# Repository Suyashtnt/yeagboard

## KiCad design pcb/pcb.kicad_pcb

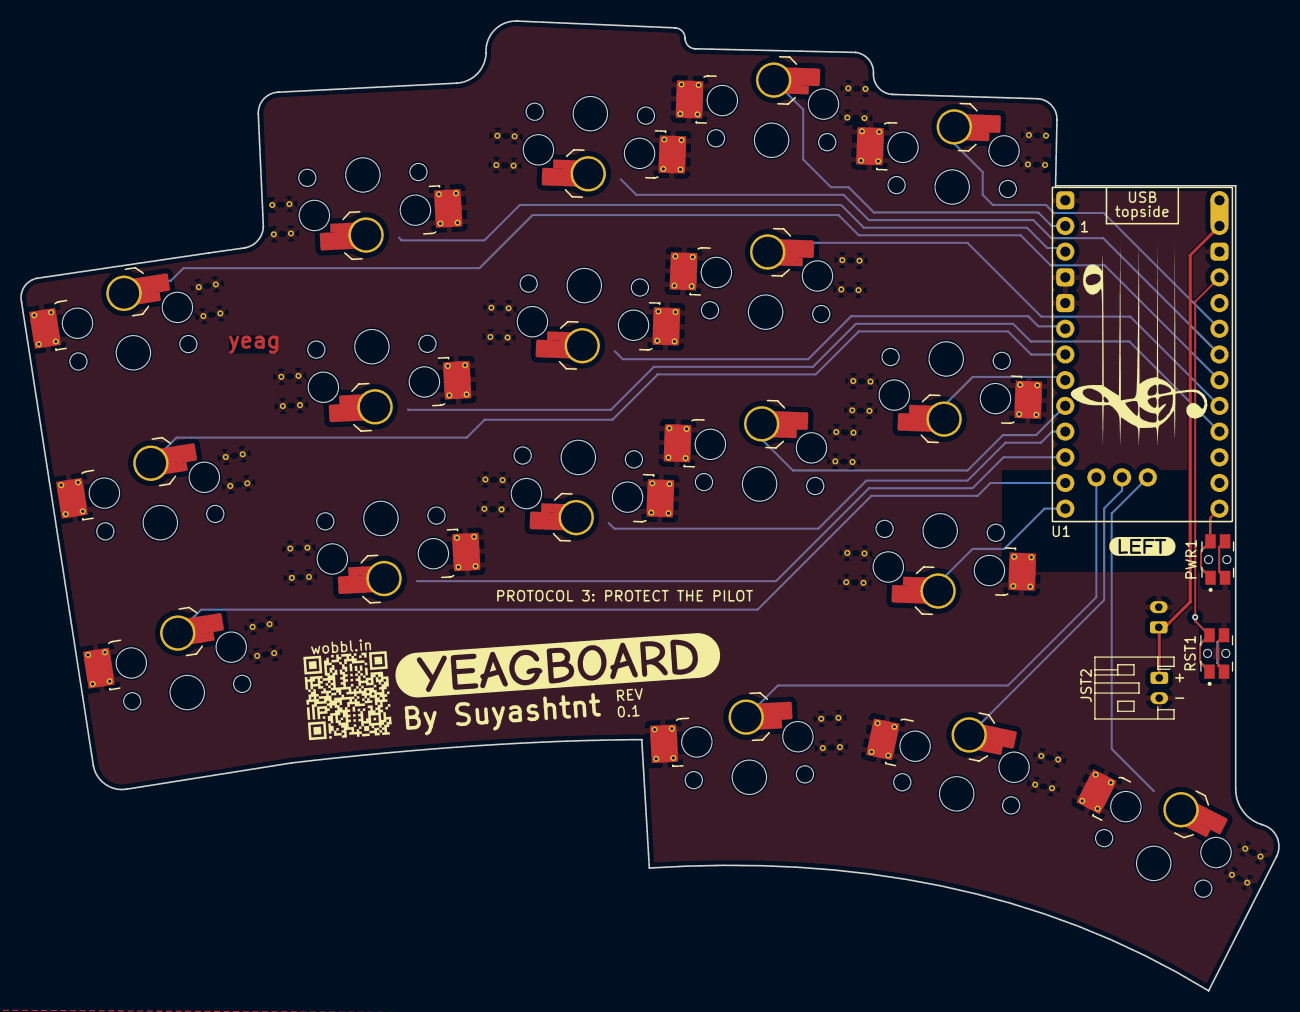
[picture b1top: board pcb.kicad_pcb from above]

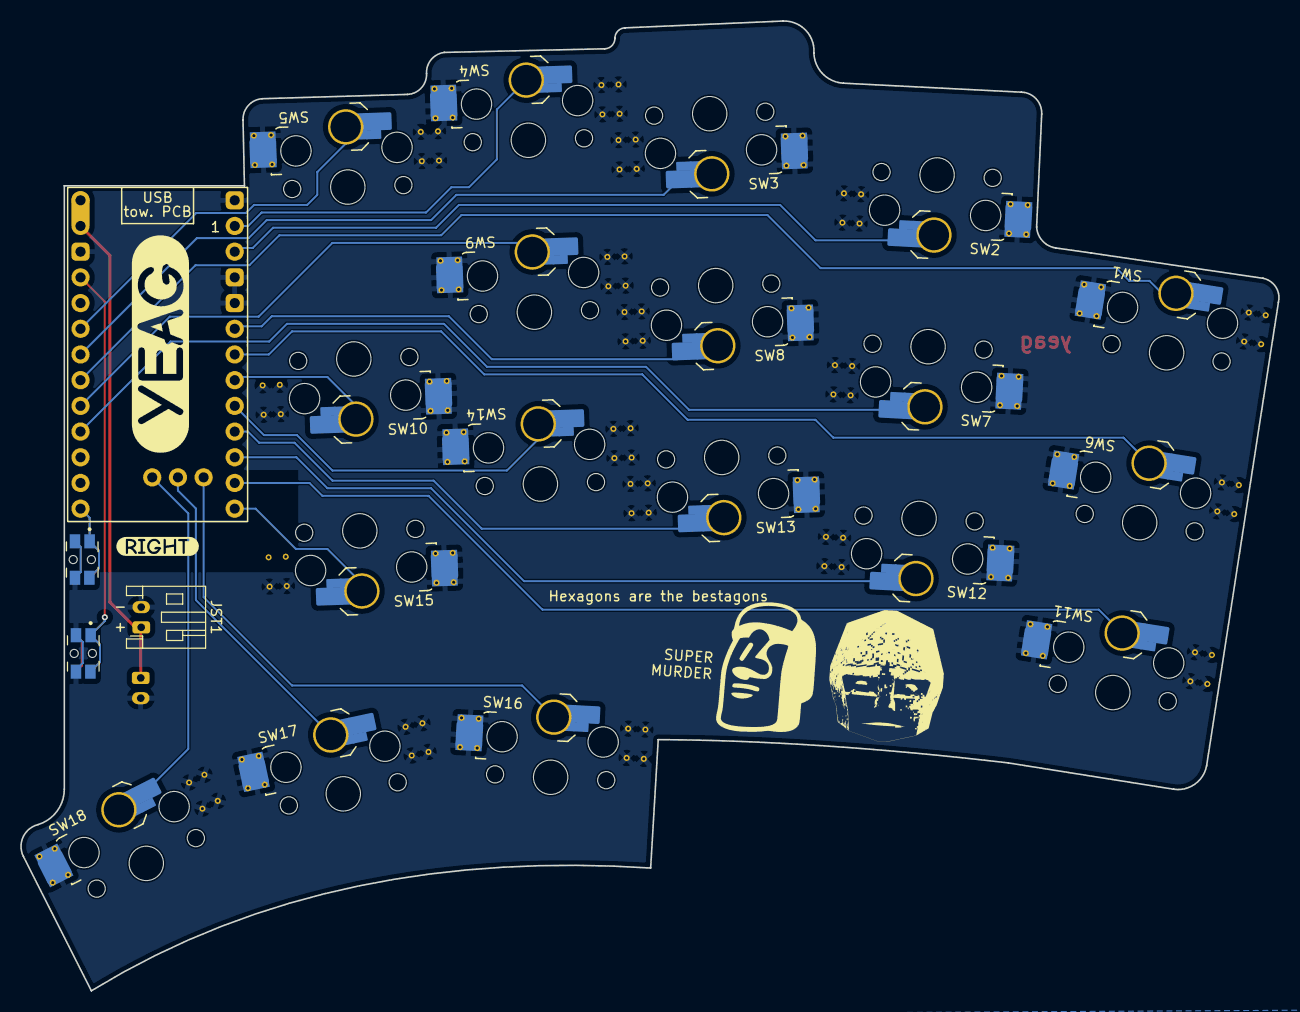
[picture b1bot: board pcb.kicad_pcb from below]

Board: 2 copper layers, 124.3 x 95.9 mm, 28 parts (21 on the bottom side), 22 nets.

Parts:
JST1, JST2: Conn_01x02; JST_PH_S2B-PH-K_1x02_P2.00mm_Horizontal
PWR1: EVQ-P7C01P; EVQ-P7C-Reversible
QR*****: WobblQR
RST1: EVQ-P7C01P; EVQ-P7C-Reversible
SW1, SW2, SW3, SW4, SW5, SW6, SW7, SW8, SW9, SW10, SW11, SW12, SW13, SW14, SW15, SW16, SW17, SW18: SW_Push; Choc-V1-HS-Reversible
U1: SuperMini nRF52840; SuperMini_nRF52840_AH_Reversible
kibuzzard-671E83A0: G***; kibuzzard-671E83A0
kibuzzard-671E83AE: G***; kibuzzard-671E83AE
kibuzzard-671E828F: G***; kibuzzard-671E828F
kibuzzard-671E8171: G***; kibuzzard-671E8171

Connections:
+BATT: JST1.1, JST2.1, U1.13 (BAT+), U1.29 (BAT+)
GND: JST1.2, JST2.2, PWR1.2, RST1.2, SW1.2, SW2.2, SW3.2, SW4.2, SW5.2, SW6.2, SW7.2, SW8.2, SW9.2, SW10.2, SW11.2, SW12.2, SW13.2, SW14.2, SW15.2, SW16.2, SW17.2, SW18.2, U1.3 (GND), U1.4 (GND), U1.14 (GND), U1.28 (GND)
PWR-BTN: PWR1.1, U1.24 (P0.09-LF)
RST: RST1.1, U1.15 (RST)
Switch1: SW1.1, U1.19 (P0.02-LF)
Switch2: SW2.1, U1.2 (P0.08)
Switch3: SW3.1, U1.18 (P0.29-LF)
Switch4: SW4.1, U1.1 (P0.06)
Switch5: SW5.1, U1.17 (P0.31-LF)
Switch6: SW6.1, U1.6 (P0.20)
Switch7: SW7.1, U1.21 (P1.13-LF)
Switch8: SW8.1, U1.5 (P0.17)
Switch9: SW9.1, U1.20 (P1.15-LF)
Switch10: SW10.1, U1.7 (P0.22)
Switch11: SW11.1, U1.11 (P1.04-LF)
Switch12: SW12.1, U1.10 (P0.11)
Switch13: SW13.1, U1.9 (P1.00)
Switch14: SW14.1, U1.8 (P0.24)
Switch15: SW15.1, U1.12 (P1.06-LF)
Switch16: SW16.1, U1.25 (P1.01-LF)
Switch17: SW17.1, U1.26 (P1.02-LF)
Switch18: SW18.1, U1.27 (P1.07-LF)

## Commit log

2024-10-27 feat: initial commit
2024-10-28 feat: new hotswap footprint + routing
2024-10-28 fix: readd QR code
2024-10-29 feat: new reversible v1 design
